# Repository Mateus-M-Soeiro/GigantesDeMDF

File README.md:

<h1 align= "center">GigantesDeMDF</h1>

Projeto referente a disciplina de Programação de Hardware, 6° Semestre, Engenharia de Computação.

## Participantes

- Larissa Andrade
- Isadora Bastos
- Mateus Malheiros
- Mateus Salles

## Sobre

O projeto Gigantes de MDF foi desenvolvido com o objetivo de colocar em prática os conhecimentos lecionados durante o semestre.

Toda a programação do projeto foi baseada no datasheet do microcontrolador Atmega328p.

A linguagem de programação utilizada foi a C.

Ficou evidente o uso eficiente e otimizado do microcontrolador Atmega328p, por meio de uma programação limpa e dinâmica.

## Componentes e esquemático

|   Componentes   | Quantidade |
|:---------------:|:----------:|
| Arduino NANO    |     x1     |
| Células de lítio|     x4     |
| Borne           |     x22    |
| Botão           |     x1     |
| Capacitor 10mF  |     x1     |
| Chave           |     x1     |
| Laser 5mW       |     x1     |
| L293D           |     x1     |
| Leds            |     x4     |
| Motor DC        |     x2     |
| Resistor 330    |     x4     |
| Resistor 4.7K   |     x1     |
| Resistor 1K     |     x1     |
| Resistor 10K    |     x1     |
| Rodas           |     x2     |
| TIP41C          |     x1     |
| Módulo JoyStick |     x1     |

## Esquemático do circuito

## Softwares

- Arduino IDE
- Doxygen
- Flashprint
- Fusion 360
- KiCad
- PCB-Proto Studio 
- RDWorks
- SimulIDE

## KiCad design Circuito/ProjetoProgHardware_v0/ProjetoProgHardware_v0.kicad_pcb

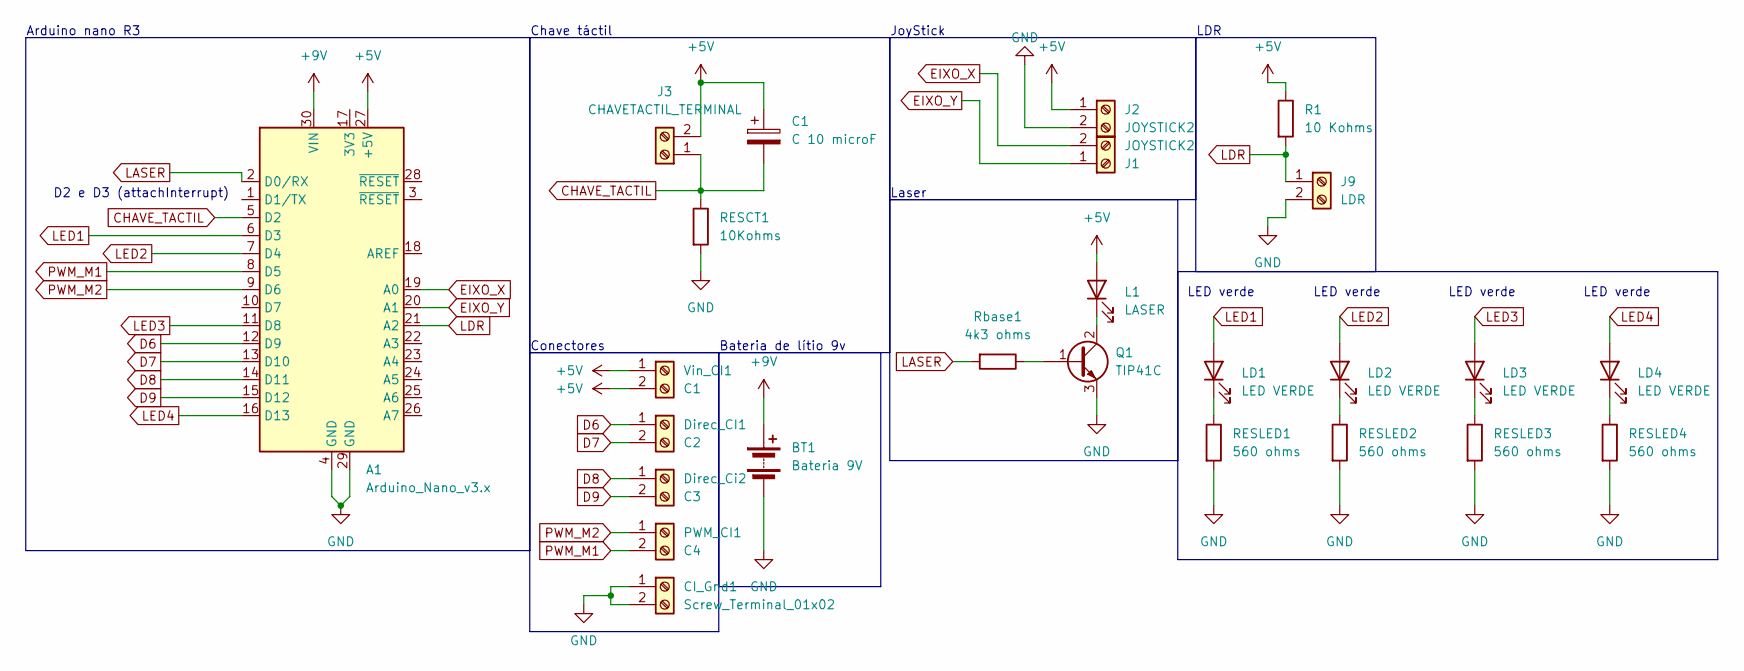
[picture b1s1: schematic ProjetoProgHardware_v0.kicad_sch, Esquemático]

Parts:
A1: Arduino_Nano_v3.x; Arduino_Nano
BT1: Bateria 9V; TerminalBlock_Altech_AK300-2_P5.00mm
C1: C 10 microF; CP_Radial_D4.0mm_P2.00mm
CI_Gnd1: Screw_Terminal_01x02; TerminalBlock_Altech_AK300-2_P5.00mm
Direc_CI1: C2; TerminalBlock_Altech_AK300-2_P5.00mm
Direc_Ci2: C3; TerminalBlock_Altech_AK300-2_P5.00mm
J1, J2: JOYSTICK2; TerminalBlock_Altech_AK300-2_P5.00mm
J3: CHAVETACTIL_TERMINAL; TerminalBlock_Altech_AK300-2_P5.00mm
J9: LDR; TerminalBlock_Altech_AK300-2_P5.00mm
L1: LASER; TerminalBlock_Altech_AK300-2_P5.00mm
LD1, LD2, LD3, LD4: LED VERDE; TerminalBlock_Altech_AK300-2_P5.00mm
PWM_CI1: C4; TerminalBlock_Altech_AK300-2_P5.00mm
Q1: TIP41C; TO-220-3_Vertical
R1: 10 Kohms; R_Axial_DIN0204_L3.6mm_D1.6mm_P5.08mm_Horizontal
RESCT1: 10Kohms; R_Axial_DIN0204_L3.6mm_D1.6mm_P5.08mm_Horizontal
RESLED1, RESLED2, RESLED3, RESLED4: 560 ohms; R_Axial_DIN0204_L3.6mm_D1.6mm_P5.08mm_Horizontal
Rbase1: 4k3 ohms; R_Axial_DIN0204_L3.6mm_D1.6mm_P5.08mm_Horizontal
Vin_CI1: C1; TerminalBlock_Altech_AK300-2_P5.00mm

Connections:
+5V: A1.27 (+5V), C1.1, J2.1, J3.2, L1.2 (A), R1.1, Vin_CI1.1, Vin_CI1.2
+9V: A1.30 (VIN), BT1.1 (+)
CHAVE_TACTIL: A1.5 (D2), C1.2, J3.1, RESCT1.1
D6: A1.12 (D9), Direc_CI1.1
D7: A1.13 (D10), Direc_CI1.2
D8: A1.14 (D11), Direc_Ci2.1
D9: A1.15 (D12), Direc_Ci2.2
EIXO_X: A1.19 (A0), J1.2
EIXO_Y: A1.20 (A1), J1.1
GND: A1.4 (GND), A1.29 (GND), BT1.2 (-), CI_Gnd1.1, CI_Gnd1.2, J2.2, J9.2, Q1.3 (E), RESCT1.2, RESLED1.2, RESLED2.2, RESLED3.2, RESLED4.2
LASER: A1.2 (D0/RX), Rbase1.2
LDR: A1.21 (A2), J9.1, R1.2
LED1: A1.6 (D3), LD1.2 (A)
LED2: A1.7 (D4), LD2.2 (A)
LED3: A1.11 (D8), LD3.2 (A)
LED4: A1.16 (D13), LD4.2 (A)
unnamed: L1.1 (K), Q1.2 (C)
unnamed: LD1.1 (K), RESLED1.1
unnamed: LD2.1 (K), RESLED2.1
unnamed: LD3.1 (K), RESLED3.1
unnamed: LD4.1 (K), RESLED4.1
unnamed: Q1.1 (B), Rbase1.1
PWM_M1: A1.8 (D5), PWM_CI1.2
PWM_M2: A1.9 (D6), PWM_CI1.1

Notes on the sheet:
LED verde
Chave táctil
Arduino nano R3
Bateria de lítio 9v
Conectores
LDR
D2 e D3 (attachInterrupt)
Laser
JoyStick

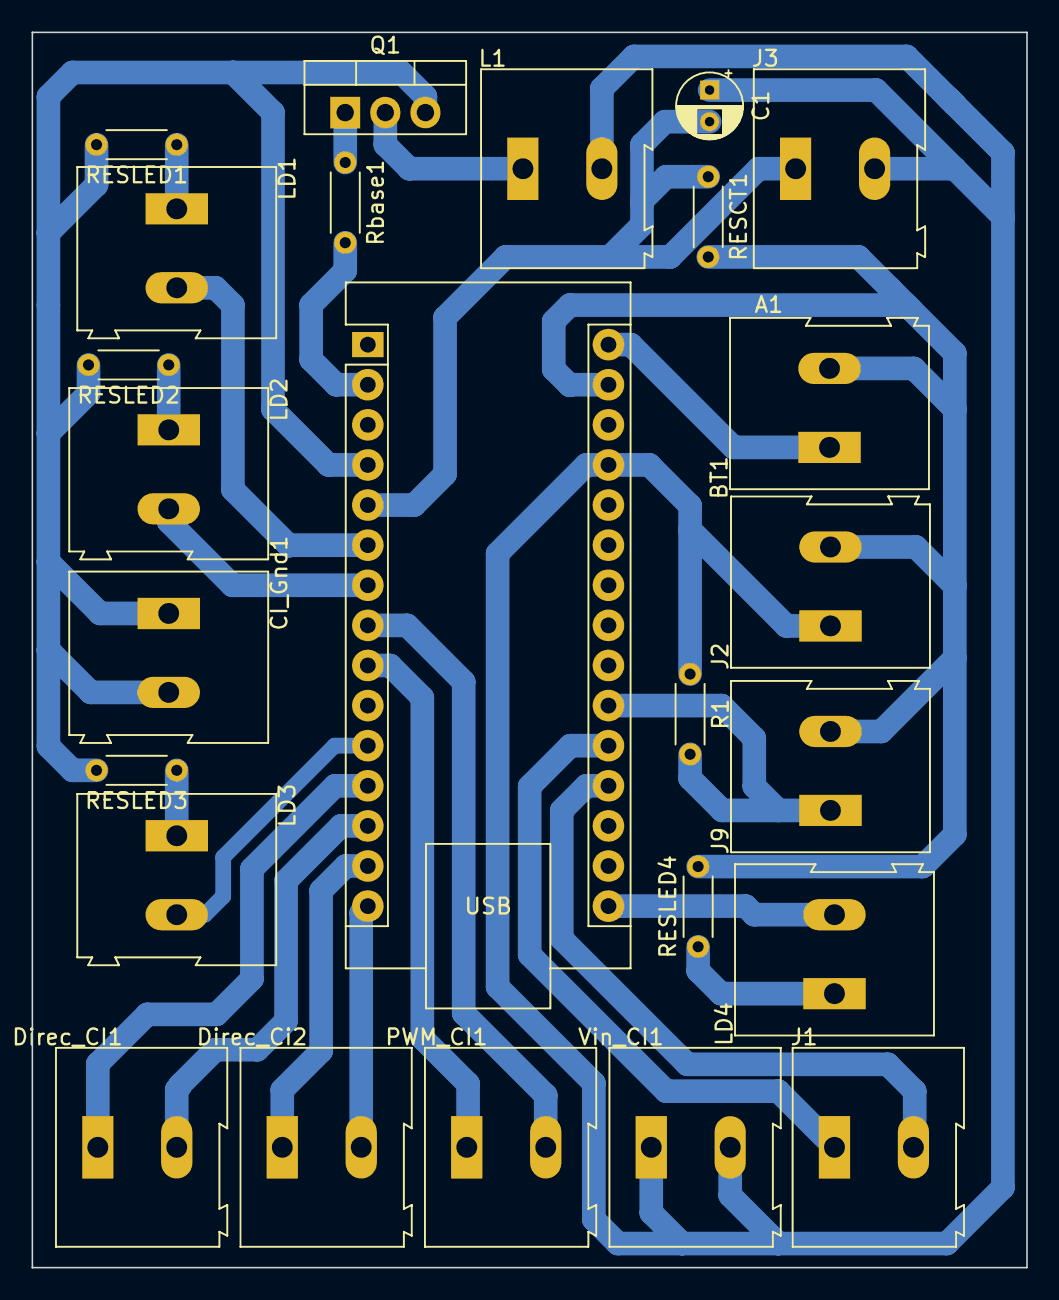
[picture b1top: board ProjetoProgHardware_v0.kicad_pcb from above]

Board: 2 copper layers, 63.0 x 78.2 mm, 25 parts (0 on the bottom side), 24 nets.

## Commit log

2023-11-15 README.md atualizado
2023-11-22 feat: Criacao do Codigo base em C
    Criação do código base para o desenvolvimento do projeto
2023-11-24 feat: adicionado função para alternar portas ADC
2023-11-24 feat: Função de movimento
    Foi adicionada a rotina na função main para que o robo se movimente de acordo com o valor das portas A0 e A1
2023-11-25 Update README.md
    Atualizando o status do projeto.
2023-11-25 Update README.md
    adicionado esquemático do circuito
2023-11-25 feat: Código final
    that's all folks!
2023-11-25 Documentação do projeto
2023-11-25 Documentação em doxygen
2023-11-25 Esquemático e layout do circuito
2023-11-28 codigo finalizado
    Código 99% funcional, faltando configurar a velocidade do PWM
